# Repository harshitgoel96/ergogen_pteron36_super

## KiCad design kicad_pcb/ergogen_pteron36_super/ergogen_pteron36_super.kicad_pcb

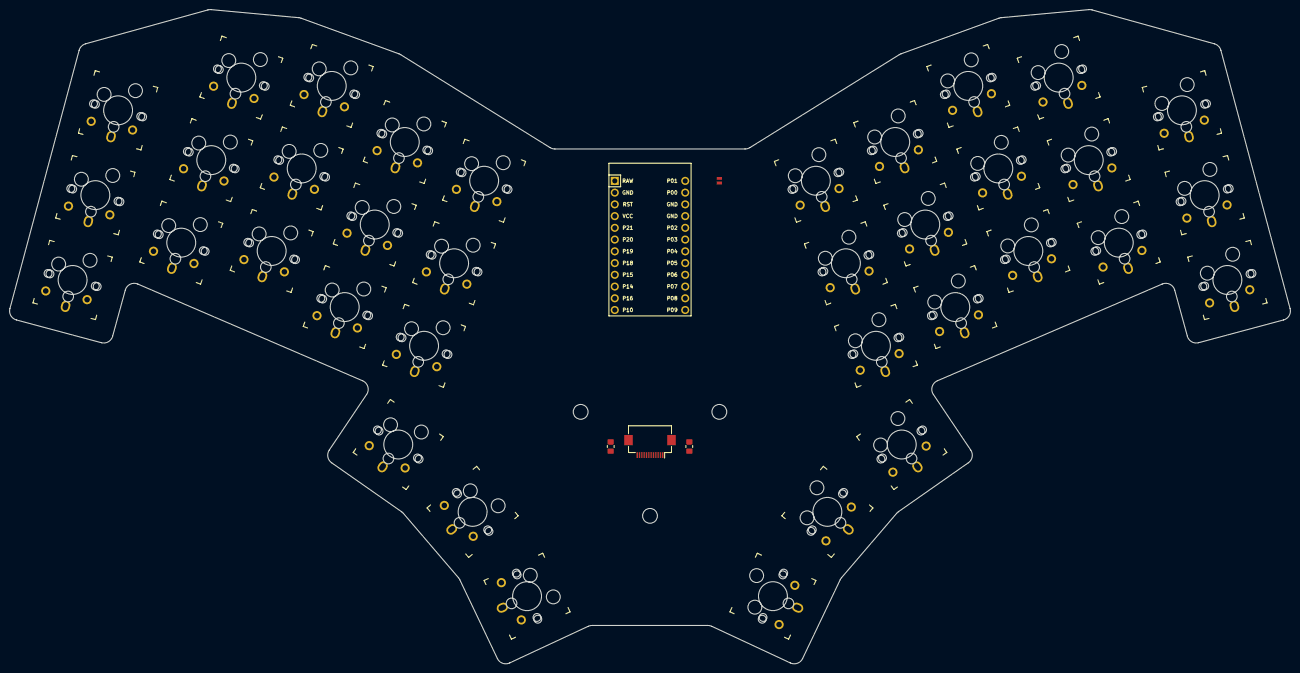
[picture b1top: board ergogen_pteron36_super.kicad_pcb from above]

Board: 2 copper layers, 277.1 x 141.5 mm, 42 parts (0 on the bottom side), 19 nets, no tracks yet.

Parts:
FC1: Hirose_FH12-12S-0.5SH_1x12-1MP_P0.50mm_Horizontal
J1, J2: Jumper
MCU1: ProMicro
R1, R2: R_0805; R_0805_2012Metric_Pad1.20x1.40mm_HandSolder
key1, key2, key3, key4, key5, key6, key7, key8, key9, key10, key11, key12, key13, key14, key15, key16, key17, key18, key19, key20, key21, key22, key23, key24, key25, key26, key27, key28, key29, key30, key31, key32, key33, key34, key35, key36: Kailh_socket_MX_LP

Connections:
C1: MCU1.19, key1.2, key2.2, key3.2
C2: MCU1.20, key4.2, key5.2, key6.2
C3: MCU1.21, key7.2, key8.2, key9.2, key16.2
C4: MCU1.22, key10.2, key11.2, key12.2, key17.2
C5: MCU1.23, key13.2, key14.2, key15.2, key18.2
C6: MCU1.24, key31.2, key32.2, key33.2, key36.2
C7: MCU1.12, key28.2, key29.2, key30.2, key35.2
C8: MCU1.11, key25.2, key26.2, key27.2, key34.2
C9: MCU1.10, key22.2, key23.2, key24.2
C10: MCU1.9, key19.2, key20.2, key21.2
GND: FC1.2, FC1.MP, J1.2, J2.2, MCU1.2, MCU1.15, MCU1.16
R1: MCU1.5, key3.1, key6.1, key9.1, key12.1, key15.1, key21.1, key24.1, key27.1, key30.1, key33.1
R2: MCU1.6, key2.1, key5.1, key8.1, key11.1, key14.1, key20.1, key23.1, key26.1, key29.1, key32.1
R3: MCU1.7, key1.1, key4.1, key7.1, key10.1, key13.1, key19.1, key22.1, key25.1, key28.1, key31.1
R4: MCU1.8, key16.1, key17.1, key18.1, key34.1, key35.1, key36.1
RST: J1.1, J2.1, MCU1.3
SCL: FC1.4, MCU1.18, R2.2
SDA: FC1.3, MCU1.17, R1.2
VCC: FC1.1, MCU1.4, R1.1, R2.1

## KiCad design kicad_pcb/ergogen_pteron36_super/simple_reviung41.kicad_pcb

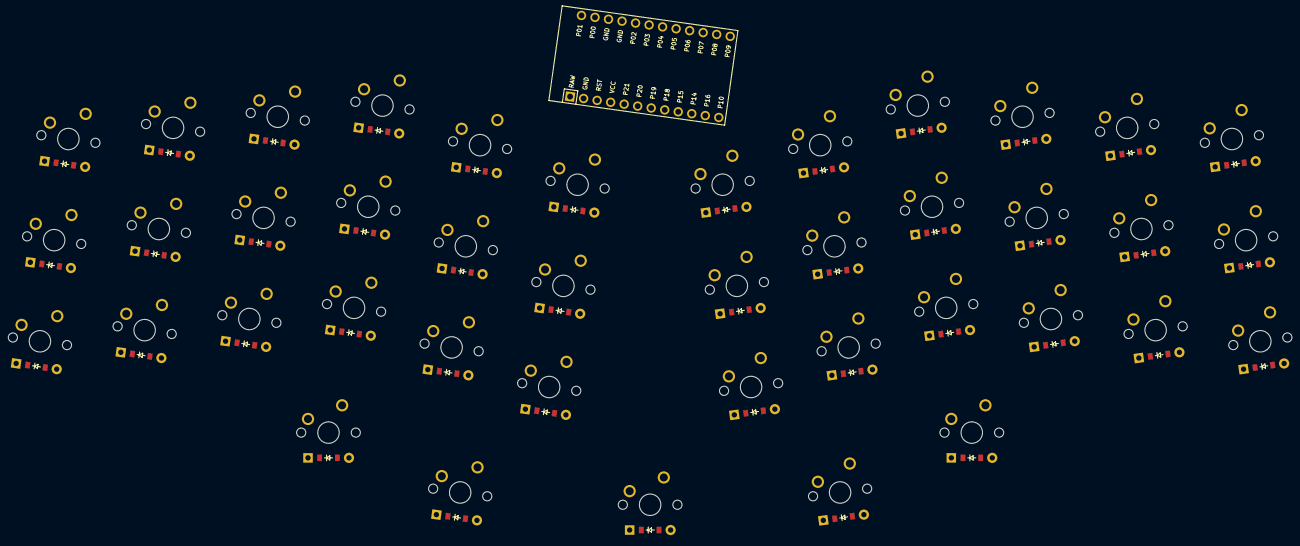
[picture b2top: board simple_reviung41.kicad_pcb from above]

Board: 2 copper layers, 83 parts (0 on the bottom side), 14 nets, no tracks yet.

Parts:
D1, D2, D3, D4, D5, D6, D7, D8, D9, D10, D11, D12, D13, D14, D15, D16, D17, D18, D19, D20, D21, D22, D23, D24, D25, D26, D27, D28, D29, D30, D31, D32, D33, D34, D35, D36, D37, D38, D39, D40, D41: ComboDiode
MCU1: ProMicro
S1, S2, S3, S4, S5, S6, S7, S8, S9, S10, S11, S12, S13, S14, S15, S16, S17, S18, S19, S20, S21, S22, S23, S24, S25, S26, S27, S28, S29, S30, S31, S32, S33, S34, S35, S36, S37, S38, S39, S40, S41: MX

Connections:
GND: MCU1.2, MCU1.15, MCU1.16
P4: MCU1.19, S1.2, S2.2, S3.2, S34.2, S35.2, S36.2
P5: MCU1.20, S4.2, S5.2, S6.2, S31.2, S32.2, S33.2
P6: MCU1.21, S7.2, S8.2, S9.2, S28.2, S29.2, S30.2, S37.2
P7: MCU1.22, S10.2, S11.2, S12.2, S25.2, S26.2, S27.2
P8: MCU1.23, S13.2, S14.2, S15.2, S22.2, S23.2, S24.2
P9: MCU1.24, S16.2, S17.2, S18.2, S19.2, S20.2, S21.2
P14: MCU1.10, S41.2
P15: MCU1.9, S39.2
P16: D37.2, D38.2, D39.2, D40.2, D41.2, MCU1.11, S37.1, S38.1, S39.1, S40.1, S41.1
P20: MCU1.6, S38.2
P21: MCU1.5, S40.2
default_default: D37.1, D38.1, D40.1
mirror_default_default: D39.1, D41.1

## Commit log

2023-05-13 initial config commit
2023-05-13 update config file
2023-05-13 update config to add FC_12 connector for trackpad.
2023-05-14 final config without outline
2023-05-14 almost final config
2023-05-14 finalised config
2023-05-19 shrinked board
2023-05-19 added screws
2023-05-19 almost final pcb
